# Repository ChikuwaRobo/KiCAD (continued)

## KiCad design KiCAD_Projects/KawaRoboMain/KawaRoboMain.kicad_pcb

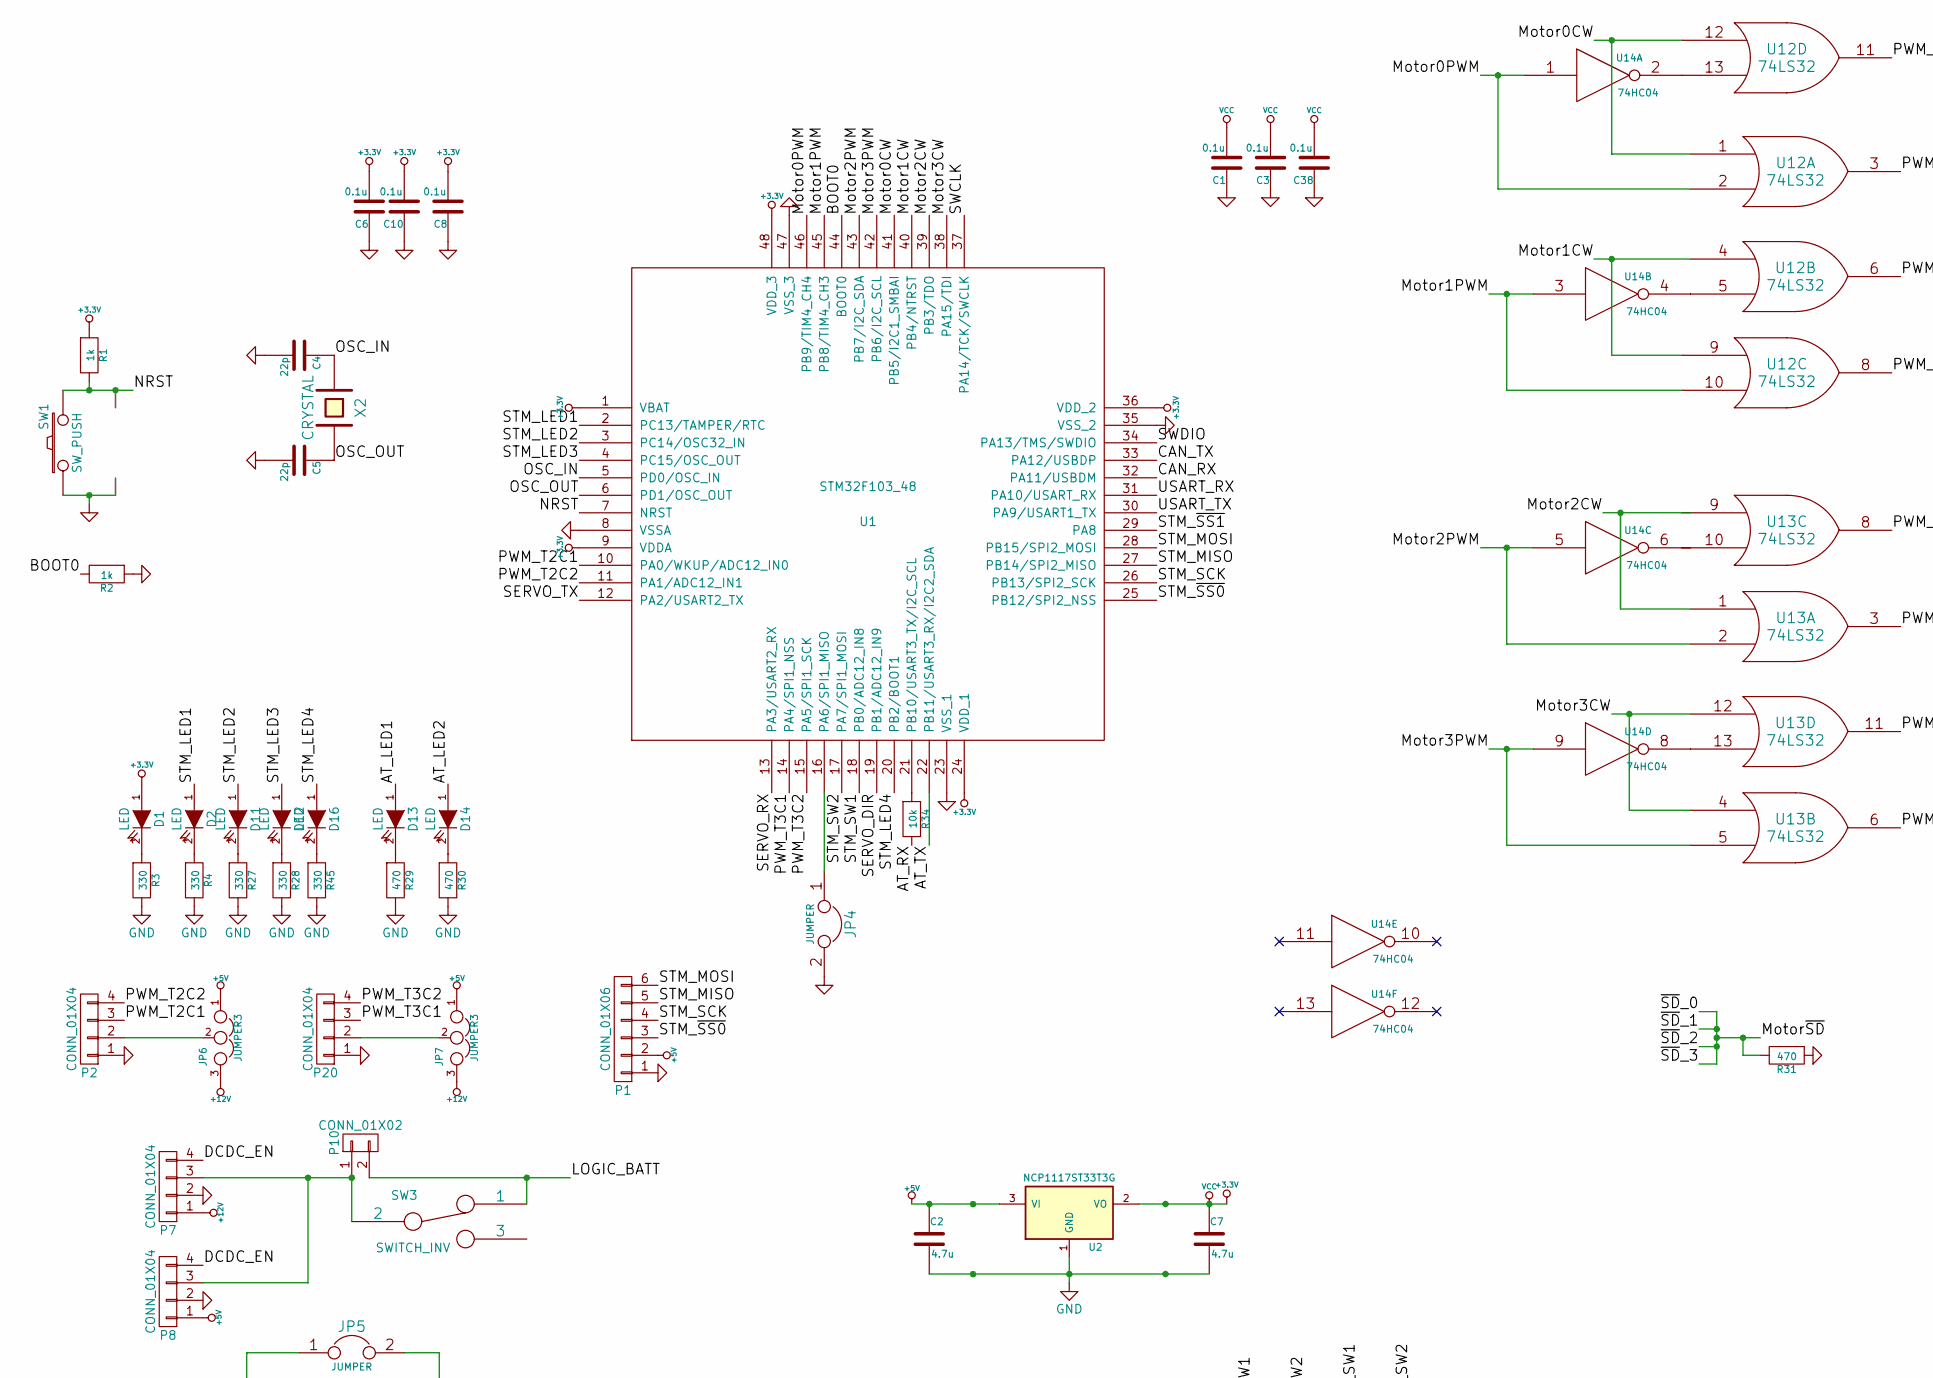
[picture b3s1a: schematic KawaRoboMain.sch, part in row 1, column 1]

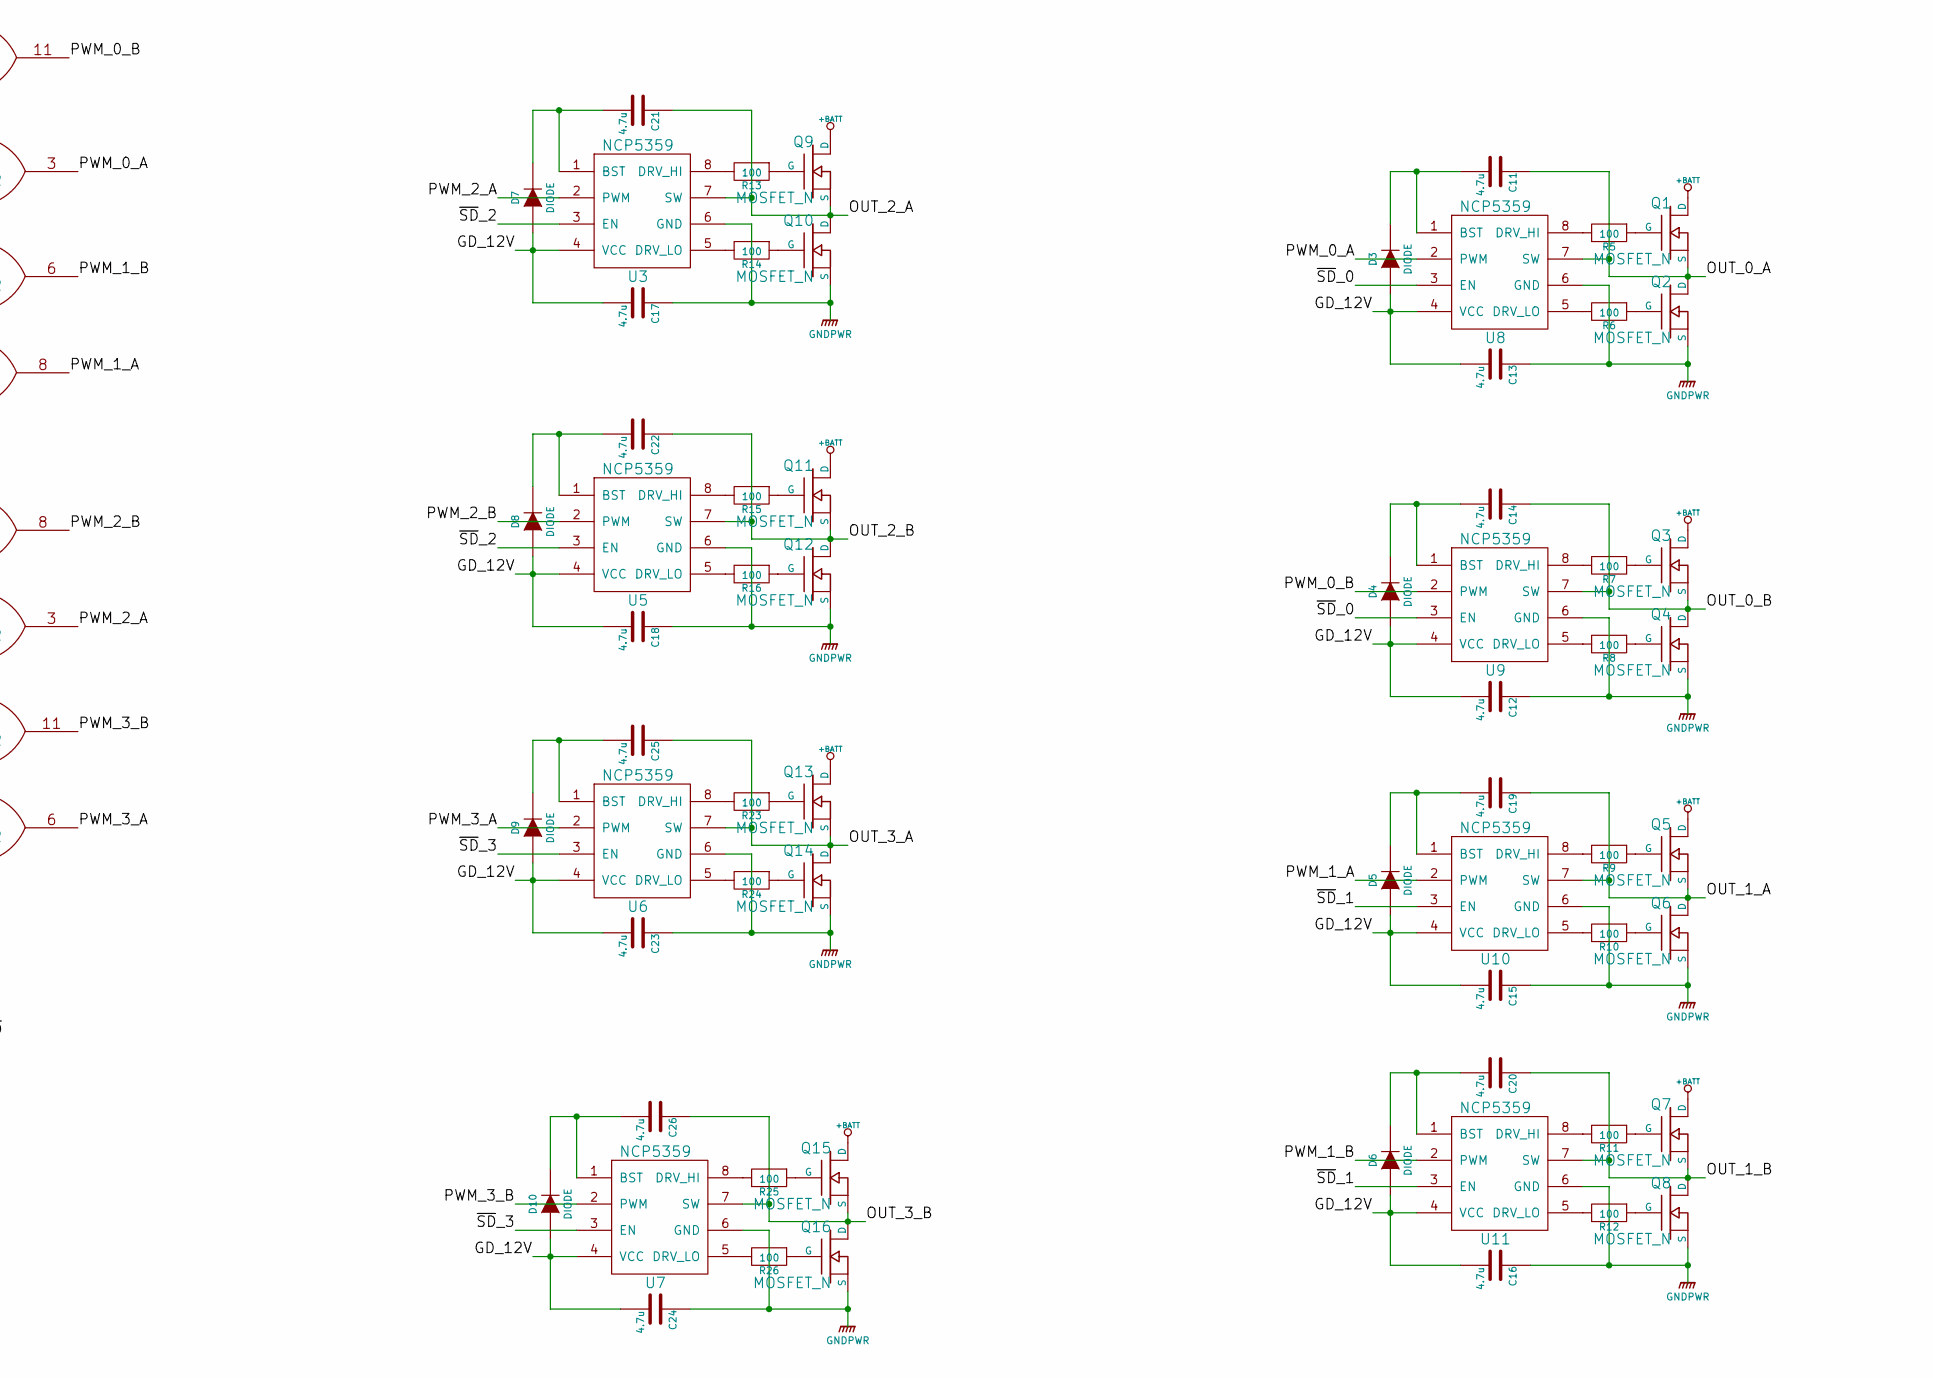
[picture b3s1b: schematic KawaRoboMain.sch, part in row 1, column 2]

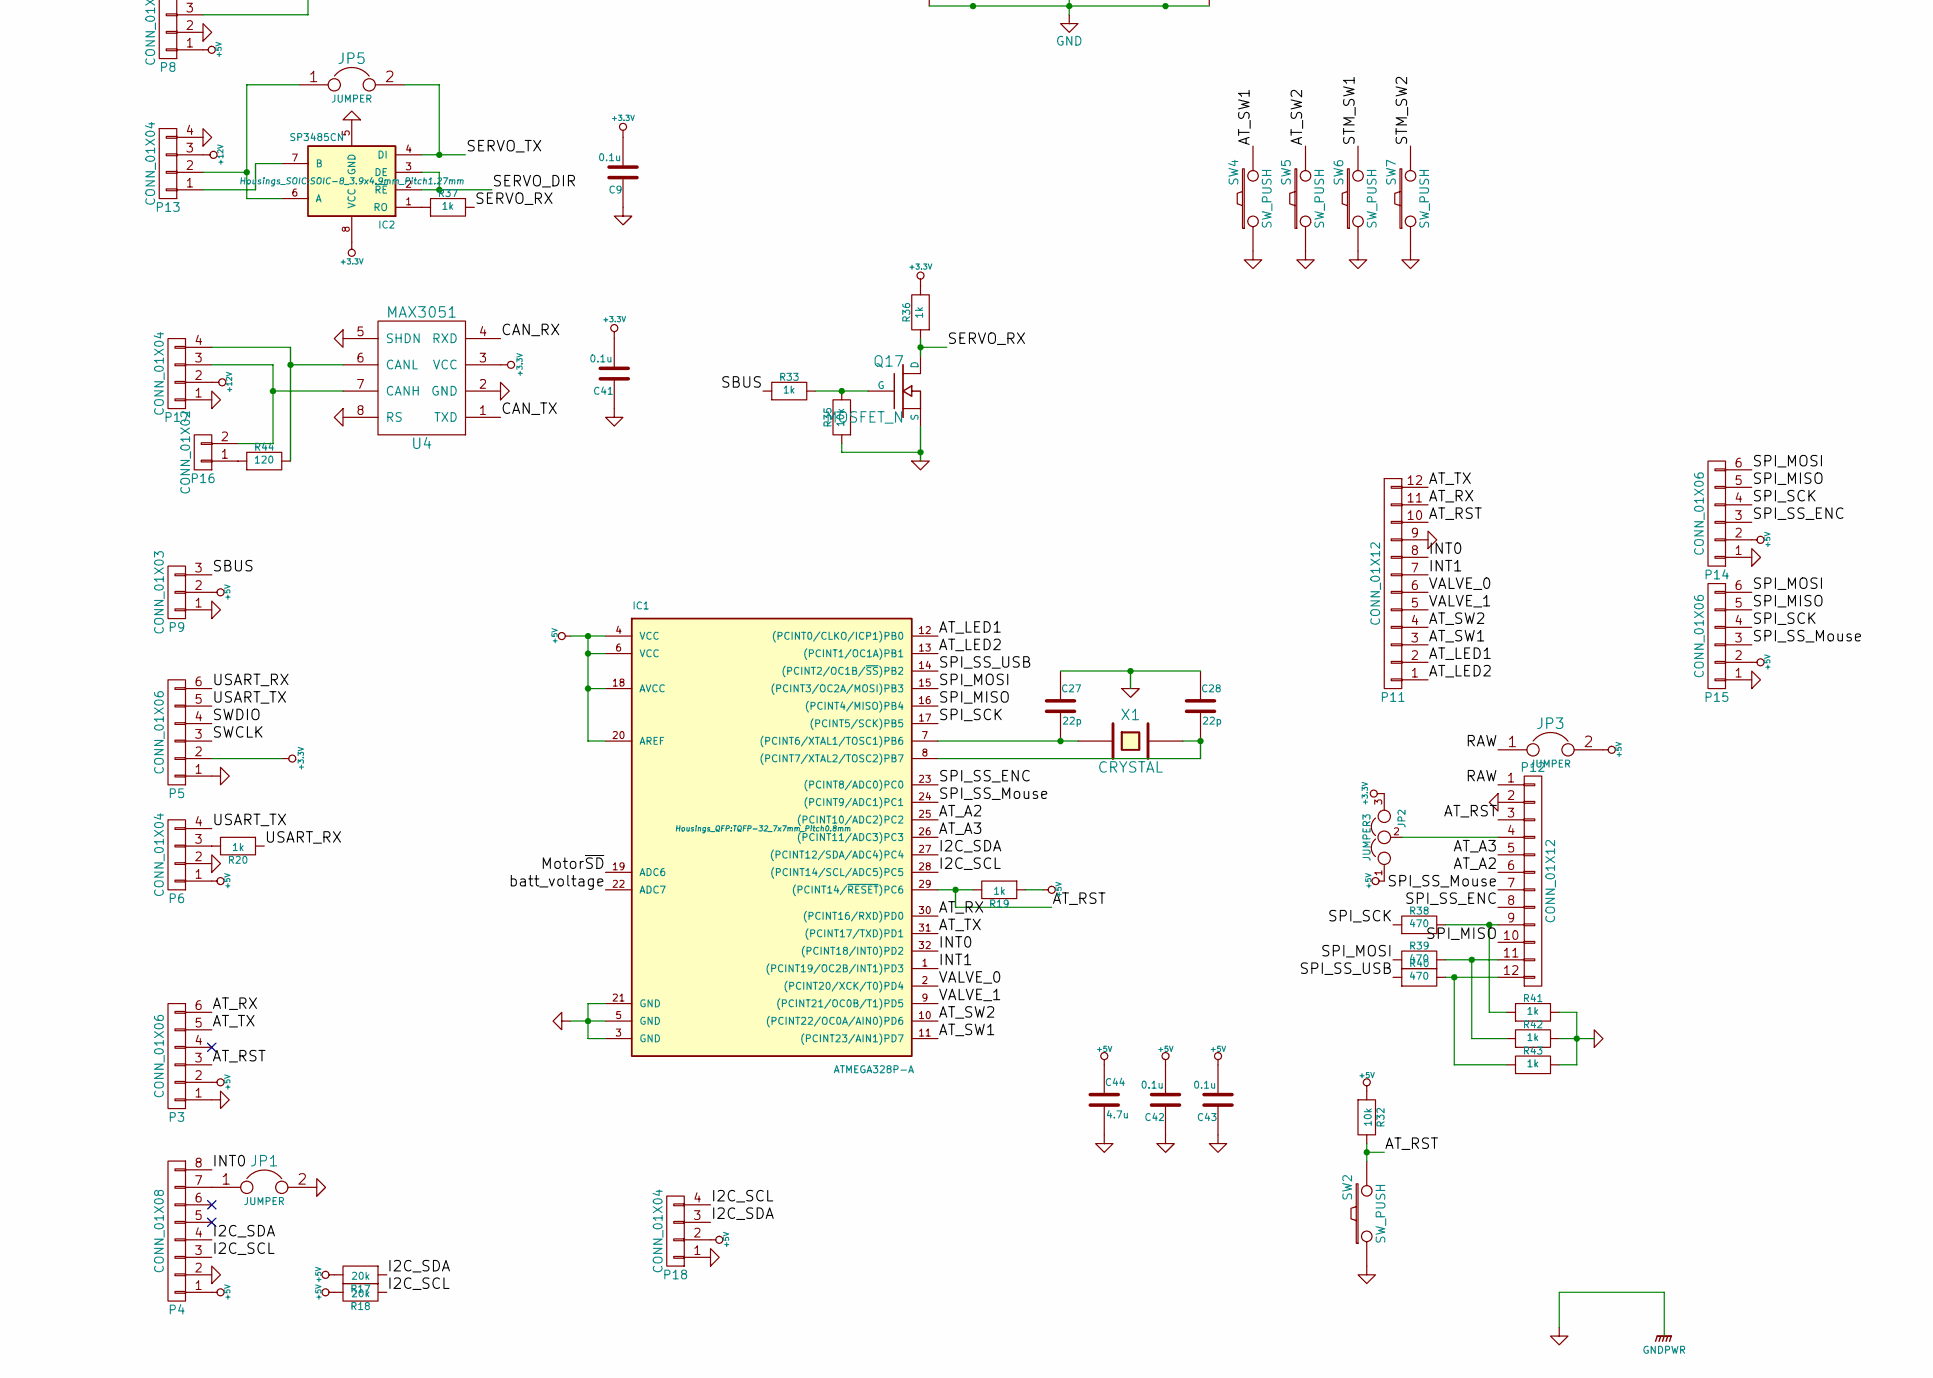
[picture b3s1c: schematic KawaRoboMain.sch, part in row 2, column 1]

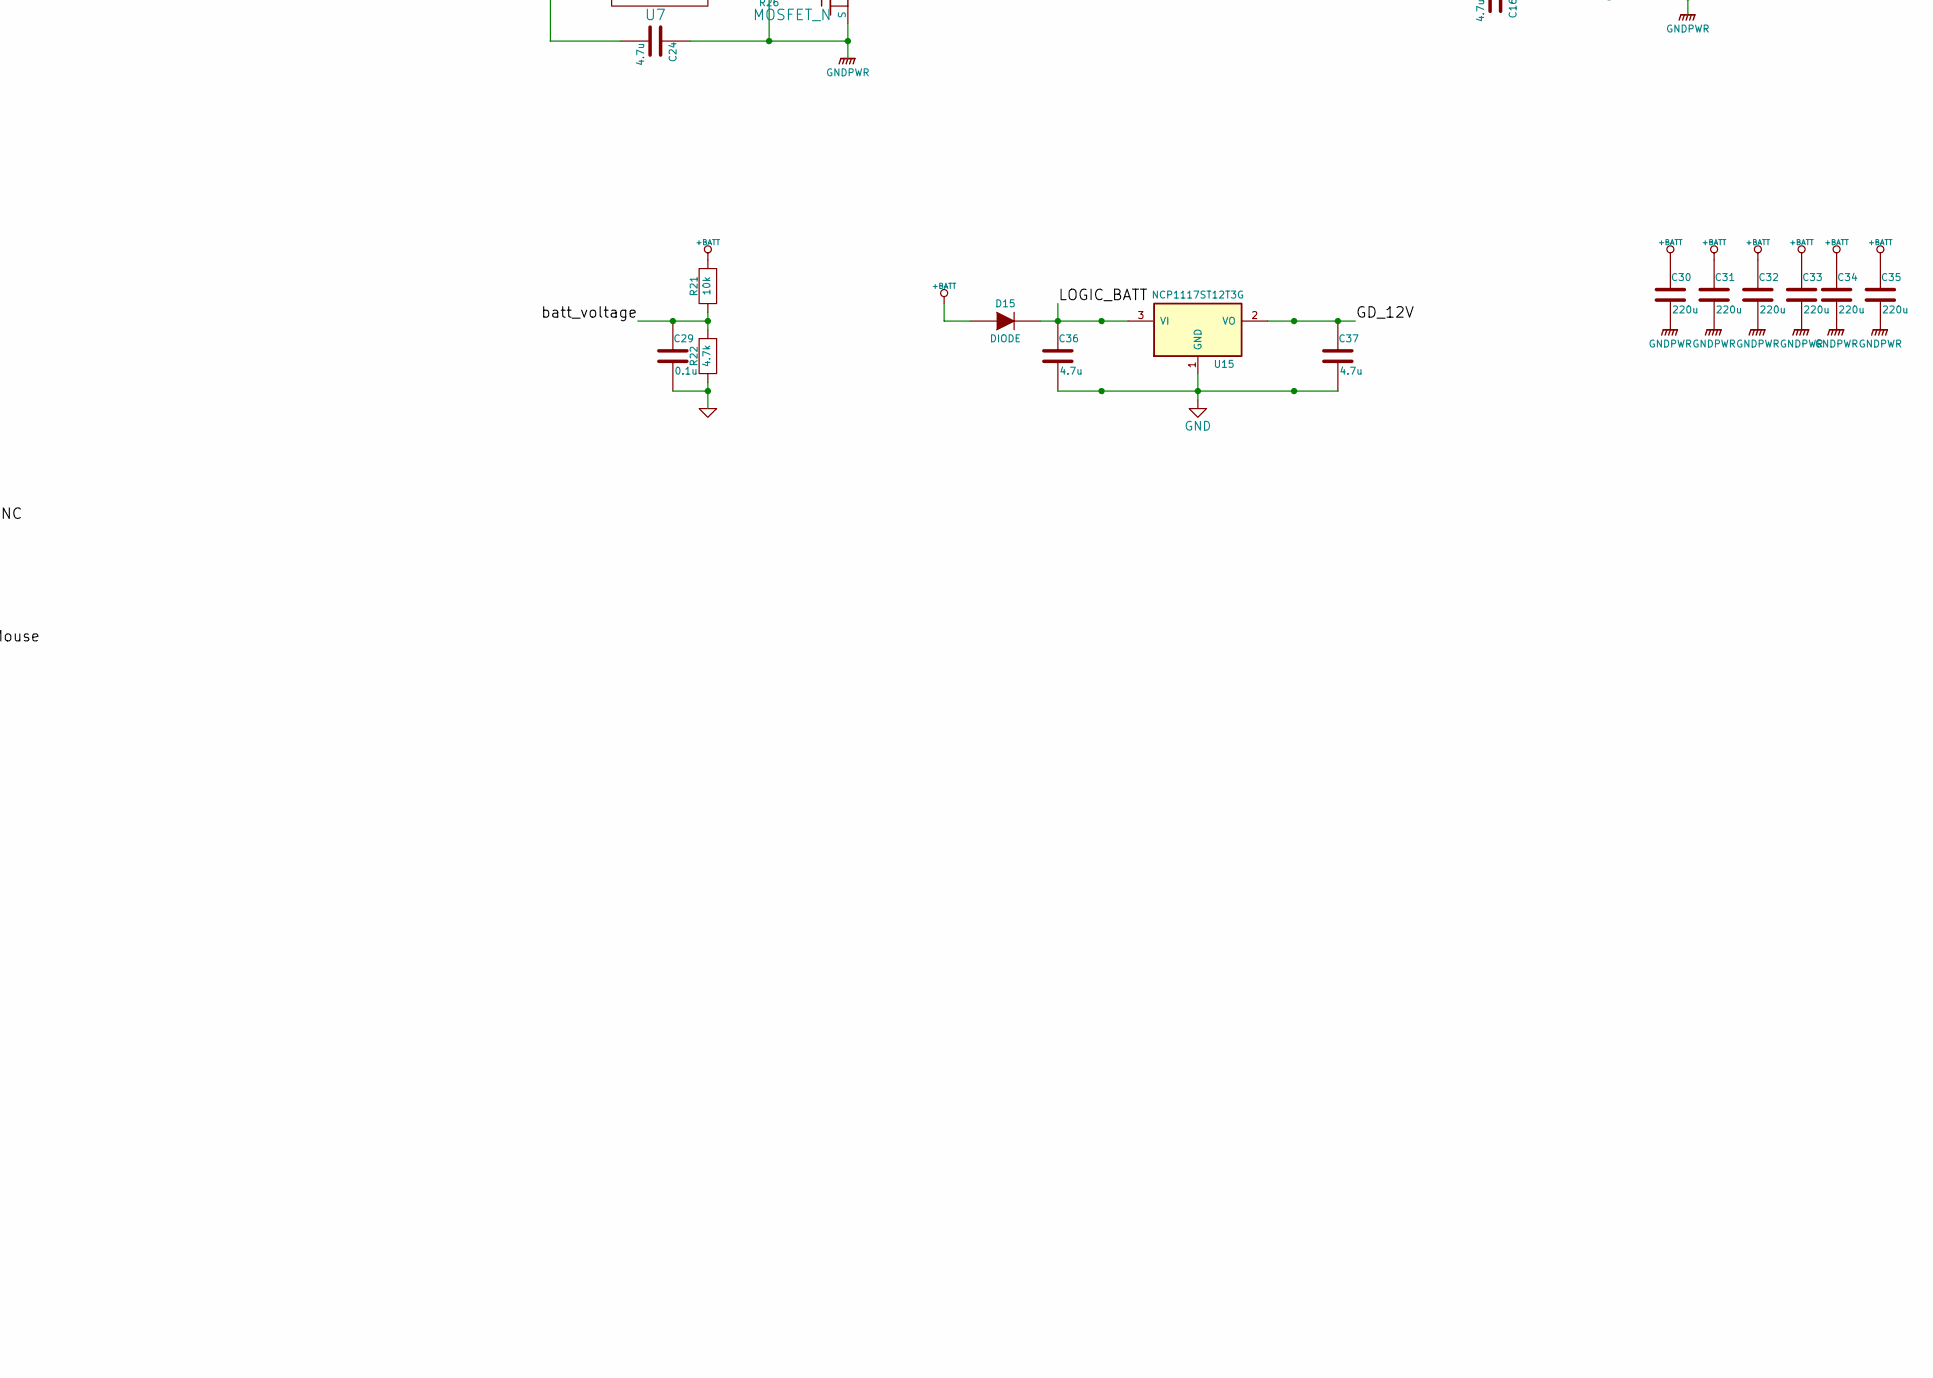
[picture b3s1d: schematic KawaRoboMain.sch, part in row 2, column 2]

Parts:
C1, C3, C6, C8, C9, C10, C29, C38, C41, C42, C43: 0.1u; C1608_WP
C2, C7, C11, C12, C13, C14, C15, C16, C17, C18, C19, C20, C21, C22, C23, C24, C25, C26, C36, C37, C44: 4.7u; C3216
C4, C5, C27, C28: 22p; C1608_WP
C30, C31, C32, C33, C34, C35: 220u; C_Radial_D10_L13_P5
D1, D2, D11, D12, D13, D14, D16: LED; LED_0805
D3, D4, D5, D6, D7, D8, D9, D10: DIODE; C2012
D15: DIODE; SOD-123
IC1: ATMEGA328P-A; TQFP-32_7x7mm_Pitch0.8mm
IC2: SP3485CN; SOIC-8_3.9x4.9mm_Pitch1.27mm
JP1, JP3, JP4, JP5: JUMPER; GS2
JP2, JP6, JP7: JUMPER3; GS3
P1, P14, P15: CONN_01X06; XA_6T
P2, P17, P20: CONN_01X04; XA_4T
P3, P5: CONN_01X06; ZH_6T
P4: CONN_01X08; Socket_Strip_Straight_1x08
P6, P7, P8, P18: CONN_01X04; Socket_Strip_Straight_1x04
P9: CONN_01X03; XA_3T
P10: CONN_01X02; XA_2T
P11, P12: CONN_01X12; Pin_Header_Straight_1x12
P13: CONN_01X04; Molex_SPOX-5267_22-03-5045_04x2.54mm_Straight
P16: CONN_01X02; Socket_Strip_Straight_1x02
Q1, Q2, Q3, Q4, Q5, Q6, Q7, Q8, Q9, Q10, Q11, Q12, Q13, Q14, Q15, Q16: MOSFET_N; SOT-428_GDS_compact
Q17: MOSFET_N; SOT-23_Handsoldering
R1, R2, R19, R20, R33, R36, R37, R41, R42, R43: 1k; C1608_WP
R3, R4, R27, R28, R45: 330; C1608_WP
R5, R6, R7, R8, R9, R10, R11, R12, R13, R14, R15, R16, R23, R24, R25, R26: 100; C1608_WP
R17, R18: 20k; C1608_WP
R21, R32, R34, R35: 10k; C1608_WP
R22: 4.7k; C1608_WP
R29, R30, R31, R38, R39, R40: 470; C1608_WP
R44: 120; C1608_WP
SW1, SW2, SW4, SW5, SW6, SW7: SW_PUSH; RP_SMD_Button
SW3: SWITCH_INV; SW_toggle_3P
U1: STM32F103_48; LQFP-48_7x7mm_Pitch0.5mm
U2: NCP1117ST33T3G; SOT-223_reg
U3, U5, U6, U7, U8, U9, U10, U11: NCP5359; SOIC-8_3.9x4.9mm_Pitch1.27mm
U4: MAX3051; SOIC-8_3.9x4.9mm_Pitch1.27mm
U12, U13: 74LS32; SOIC-14_3.9x8.7mm_Pitch1.27mm
U14: 74HC04; SOIC-14_3.9x8.7mm_Pitch1.27mm
U15: NCP1117ST12T3G; SOT-223_reg
X1: CRYSTAL; Crystal_HC50-U_Vertical
X2: CRYSTAL; ABM3_2pads

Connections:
+3.3V: C1.2, C3.2, C6.2, C7.1, C8.2, C9.2, C10.2, C38.2, C41.2, D1.1 (A), IC2.8 (VCC), JP2.3, P5.2, R1.1, R36.2, U1.1 (VBAT), U1.9 (VDDA), U1.24 (VDD_1), U1.36 (VDD_2), U1.48 (VDD_3), U2.2 (VO), U4.3 (VCC), U12.14 (VCC), U13.14 (VCC), U14.14 (VCC)
+5V: C2.1, C42.2, C43.2, C44.1, IC1.4 (VCC), IC1.6 (VCC), IC1.18 (AVCC), IC1.20 (AREF), JP2.1, JP3.2, JP6.1, JP7.1, P1.2, P3.2, P4.1, P6.1, P8.1, P9.2, P14.2, P15.2, P18.2, R17.2, R18.2, R19.1, R32.1, U2.3 (VI)
+12V: JP6.3, JP7.3, P7.1, P13.3, P17.2
+BATT: C30.1, C31.1, C32.1, C33.1, C34.1, C35.1, D15.2 (A), Q1.D, Q3.D, Q5.D, Q7.D, Q9.D, Q11.D, Q13.D, Q15.D, R21.1
/AT_A2: IC1.25 ((PCINT10/ADC2)PC2), P12.6
/AT_A3: IC1.26 ((PCINT11/ADC3)PC3), P12.5
/AT_LED1: D13.1 (A), IC1.12 ((PCINT0/CLKO/ICP1)PB0), P11.2
/AT_LED2: D14.1 (A), IC1.13 ((PCINT1/OC1A)PB1), P11.1
/AT_RST: IC1.29 ((PCINT14/~RESET~)PC6), P3.3, P11.10, P12.3, R19.2, R32.2, SW2.2
/AT_RX: IC1.30 ((PCINT16/RXD)PD0), P3.6, P11.11, R34.2
/AT_SW1: IC1.11 ((PCINT23/AIN1)PD7), P11.3, SW4.2
/AT_SW2: IC1.10 ((PCINT22/OC0A/AIN0)PD6), P11.4, SW5.2
/AT_TX: IC1.31 ((PCINT17/TXD)PD1), P3.5, P11.12, U1.22 (PB11/USART3_RX/I2C2_SDA)
/BOOT0: R2.2, U1.44 (BOOT0)
/CAN_RX: U1.32 (PA11/USBDM), U4.4 (RXD)
/CAN_TX: U1.33 (PA12/USBDP), U4.1 (TXD)
/DCDC_EN: P7.4, P8.4
/GD_12V: C12.2, C13.2, C15.2, C16.2, C17.2, C18.2, C23.2, C24.2, C37.1, D3.2 (A), D4.2 (A), D5.2 (A), D6.2 (A), D7.2 (A), D8.2 (A), D9.2 (A), D10.2 (A), U3.4 (VCC), U5.4 (VCC), U6.4 (VCC), U7.4 (VCC), U8.4 (VCC), U9.4 (VCC), U10.4 (VCC), U11.4 (VCC), U15.2 (VO)
/I2C_SCL: IC1.28 ((PCINT14/SCL/ADC5)PC5), P4.3, P18.4, R18.1
/I2C_SDA: IC1.27 ((PCINT12/SDA/ADC4)PC4), P4.4, P18.3, R17.1
/INT0: IC1.32 ((PCINT18/INT0)PD2), P4.8, P11.8
/INT1: IC1.1 ((PCINT19/OC2B/INT1)PD3), P11.7
/LOGIC_BATT: C36.1, D15.1 (K), P10.2, SW3.1, U15.3 (VI)
/Motor0CW: U1.41 (PB5/I2C1_SMBAI), U12.1, U12.12
/Motor0PWM: U1.46 (PB9/TIM4_CH4), U12.2, U14.1
/Motor1CW: U1.40 (PB4/NTRST), U12.4, U12.9
/Motor1PWM: U1.45 (PB8/TIM4_CH3), U12.10, U14.3
/Motor2CW: U1.39 (PB3/TDO), U13.1
/Motor2PWM: U1.43 (PB7/I2C_SDA), U13.2, U14.5
/Motor3CW: U1.38 (PA15/TDI), U13.4, U13.12
/Motor3PWM: U1.42 (PB6/I2C_SCL), U13.5, U14.9
/Motor~SD: IC1.19 (ADC6), R31.2, U3.3 (EN), U5.3 (EN), U6.3 (EN), U7.3 (EN), U8.3 (EN), U9.3 (EN), U10.3 (EN), U11.3 (EN)
/NRST: R1.2, SW1.2, U1.7 (NRST)
/OSC_IN: C4.1, U1.5 (PD0/OSC_IN), X2.1
/OSC_OUT: C5.1, U1.6 (PD1/OSC_OUT), X2.2
/OUT_0_A: C11.1, Q1.S, Q2.D, U8.7 (SW)
/OUT_0_B: C14.1, Q3.S, Q4.D, U9.7 (SW)
/OUT_1_A: C19.1, Q5.S, Q6.D, U10.7 (SW)
/OUT_1_B: C20.1, Q7.S, Q8.D, U11.7 (SW)
/OUT_2_A: C21.1, Q9.S, Q10.D, U3.7 (SW)
/OUT_2_B: C22.1, Q11.S, Q12.D, U5.7 (SW)
/OUT_3_A: C25.1, Q13.S, Q14.D, U6.7 (SW)
/OUT_3_B: C26.1, Q15.S, Q16.D, U7.7 (SW)
/PWM_0_A: U8.2 (PWM), U12.3
/PWM_0_B: U9.2 (PWM), U12.11
/PWM_1_A: U10.2 (PWM), U12.8
/PWM_1_B: U11.2 (PWM), U12.6
/PWM_2_A: U3.2 (PWM), U13.3
/PWM_2_B: U5.2 (PWM), U13.8
/PWM_3_A: U6.2 (PWM), U13.6
/PWM_3_B: U7.2 (PWM), U13.11
/PWM_T2C1: P2.3, U1.10 (PA0/WKUP/ADC12_IN0)
/PWM_T2C2: P2.4, U1.11 (PA1/ADC12_IN1)
/PWM_T3C1: P20.3, U1.14 (PA4/SPI1_NSS)
/PWM_T3C2: P20.4, U1.15 (PA5/SPI1_SCK)
/RAW: JP3.1, P12.1
/SBUS: P9.3, R33.1
/SERVO_DIR: IC2.2 (~RE~), IC2.3 (DE), U1.19 (PB1/ADC12_IN9)
/SERVO_RX: Q17.D, R36.1, R37.2, U1.13 (PA3/USART2_RX)
/SERVO_TX: IC2.4 (DI), JP5.2, U1.12 (PA2/USART2_TX)
/SPI_MISO: IC1.16 ((PCINT4/MISO)PB4), P12.10, P14.5, P15.5
/SPI_MOSI: IC1.15 ((PCINT3/OC2A/MOSI)PB3), P14.6, P15.6, R39.1
/SPI_SCK: IC1.17 ((PCINT5/SCK)PB5), P14.4, P15.4, R38.1
/SPI_SS_ENC: IC1.23 ((PCINT8/ADC0)PC0), P12.8, P14.3
/SPI_SS_Mouse: IC1.24 ((PCINT9/ADC1)PC1), P12.7, P15.3
/SPI_SS_USB: IC1.14 ((PCINT2/OC1B/~SS~)PB2), R40.1
/STM_LED1: D2.1 (A), U1.2 (PC13/TAMPER/RTC)
/STM_LED2: D11.1 (A), U1.3 (PC14/OSC32_IN)
/STM_LED3: D12.1 (A), U1.4 (PC15/OSC_OUT)
/STM_LED4: D16.1 (A), U1.20 (PB2/BOOT1)
/STM_MISO: P1.5, U1.27 (PB14/SPI2_MISO)
/STM_MOSI: P1.6, U1.28 (PB15/SPI2_MOSI)
/STM_SCK: P1.4, U1.26 (PB13/SPI2_SCK)
/STM_SW1: SW6.2, U1.18 (PB0/ADC12_IN8)
/STM_SW2: SW7.2, U1.17 (PA7/SPI1_MOSI)
/STM_~SS0: P1.3, U1.25 (PB12/SPI2_NSS)
/SWCLK: P5.3, U1.37 (PA14/TCK/SWCLK)
/SWDIO: P5.4, U1.34 (PA13/TMS/SWDIO)
/USART_RX: P5.6, R20.1, U1.31 (PA10/USART_RX)
/USART_TX: P5.5, P6.4, U1.30 (PA9/USART1_TX)
/VALVE_0: IC1.2 ((PCINT20/XCK/T0)PD4), P11.6
/VALVE_1: IC1.9 ((PCINT21/OC0B/T1)PD5), P11.5
/batt_voltage: C29.1, IC1.22 (ADC7), R21.2, R22.1
GND: C1.1, C2.2, C3.1, C4.2, C5.2, C6.1, C7.2, C8.1, C9.1, C10.1, C12.1, C13.1, C15.1, C16.1, C17.1, C18.1, C23.1, C24.1, C27.1, C28.1, C29.2, C30.2, C31.2, C32.2, C33.2, C34.2, C35.2, C36.2, C37.2, C38.1, C41.1, C42.1, C43.1, C44.2, IC1.3 (GND), IC1.5 (GND), IC1.21 (GND), IC2.5 (GND), JP1.2, JP4.2, P1.1, P2.1, P3.1, P4.2, P5.1, P6.2, P7.2, P8.2, P9.1, P11.9, P12.2, P13.4, P14.1, P15.1, P17.1, P18.1, P20.1, Q2.S, Q4.S, Q6.S, Q8.S, Q10.S, Q12.S, Q14.S, Q16.S, Q17.S, R2.1, R3.2, R4.2, R22.2, R27.2, R28.2, R29.2, R30.2, R31.1, R35.1, R41.2, R42.2, R43.2, R45.2, SW1.1, SW2.1, SW4.1, SW5.1, SW6.1, SW7.1, U1.8 (VSSA), U1.23 (VSS_1), U1.35 (VSS_2), U1.47 (VSS_3), U2.1 (GND), U3.6 (GND), U4.2 (GND), U4.5 (SHDN), U4.8 (RS), U5.6 (GND), U6.6 (GND), U7.6 (GND), U8.6 (GND), U9.6 (GND), U10.6 (GND), U11.6 (GND), U12.7 (GND), U13.7 (GND), U14.7 (GND), U15.1 (GND)
unnamed: C11.2, D3.1 (K), U8.1 (BST)
unnamed: C14.2, D4.1 (K), U9.1 (BST)
unnamed: C19.2, D5.1 (K), U10.1 (BST)
unnamed: C20.2, D6.1 (K), U11.1 (BST)
unnamed: C21.2, D7.1 (K), U3.1 (BST)
unnamed: C22.2, D8.1 (K), U5.1 (BST)
unnamed: C25.2, D9.1 (K), U6.1 (BST)
unnamed: C26.2, D10.1 (K), U7.1 (BST)
unnamed: C27.2, IC1.7 ((PCINT6/XTAL1/TOSC1)PB6), X1.1
unnamed: C28.2, IC1.8 ((PCINT7/XTAL2/TOSC2)PB7), X1.2
unnamed: D1.2 (K), R3.1
unnamed: D2.2 (K), R4.1
unnamed: D11.2 (K), R27.1
unnamed: D12.2 (K), R28.1
unnamed: D13.2 (K), R29.1
unnamed: D14.2 (K), R30.1
unnamed: D16.2 (K), R45.1
unnamed: IC2.1 (RO), R37.1
unnamed: IC2.6 (A), JP5.1, P13.2
unnamed: IC2.7 (B), P13.1
unnamed: JP1.1, P4.7
unnamed: JP2.2, P12.4
unnamed: JP4.1, U1.16 (PA6/SPI1_MISO)
unnamed: JP6.2, P2.2
unnamed: JP7.2, P20.2
unnamed: P6.3, R20.2
unnamed: P7.3, P8.3, P10.1, SW3.2
unnamed: P12.9, R38.2, R41.1
unnamed: P12.11, R39.2, R42.1
unnamed: P12.12, R40.2, R43.1
unnamed: P16.1, R44.1
unnamed: P16.2, P17.3, U4.7 (CANH)
unnamed: P17.4, R44.2, U4.6 (CANL)
unnamed: Q1.G, R5.1
unnamed: Q2.G, R6.1
unnamed: Q3.G, R7.1
unnamed: Q4.G, R8.1
unnamed: Q5.G, R9.1
unnamed: Q6.G, R10.1
unnamed: Q7.G, R11.1
unnamed: Q8.G, R12.1
unnamed: Q9.G, R13.1
unnamed: Q10.G, R14.1
unnamed: Q11.G, R15.1
unnamed: Q12.G, R16.1
unnamed: Q13.G, R23.1
unnamed: Q14.G, R24.1
unnamed: Q15.G, R25.1
unnamed: Q16.G, R26.1
unnamed: Q17.G, R33.2, R35.2
unnamed: R5.2, U8.8 (DRV_HI)
unnamed: R6.2, U8.5 (DRV_LO)
unnamed: R7.2, U9.8 (DRV_HI)
unnamed: R8.2, U9.5 (DRV_LO)
unnamed: R9.2, U10.8 (DRV_HI)
unnamed: R10.2, U10.5 (DRV_LO)
unnamed: R11.2, U11.8 (DRV_HI)
unnamed: R12.2, U11.5 (DRV_LO)
unnamed: R13.2, U3.8 (DRV_HI)
unnamed: R14.2, U3.5 (DRV_LO)
unnamed: R15.2, U5.8 (DRV_HI)
unnamed: R16.2, U5.5 (DRV_LO)
unnamed: R23.2, U6.8 (DRV_HI)
unnamed: R24.2, U6.5 (DRV_LO)
unnamed: R25.2, U7.8 (DRV_HI)
unnamed: R26.2, U7.5 (DRV_LO)
unnamed: R34.1, U1.21 (PB10/USART3_TX/I2C_SCL)
unnamed: U12.5, U14.4
unnamed: U12.13, U14.2
unnamed: U13.13, U14.8

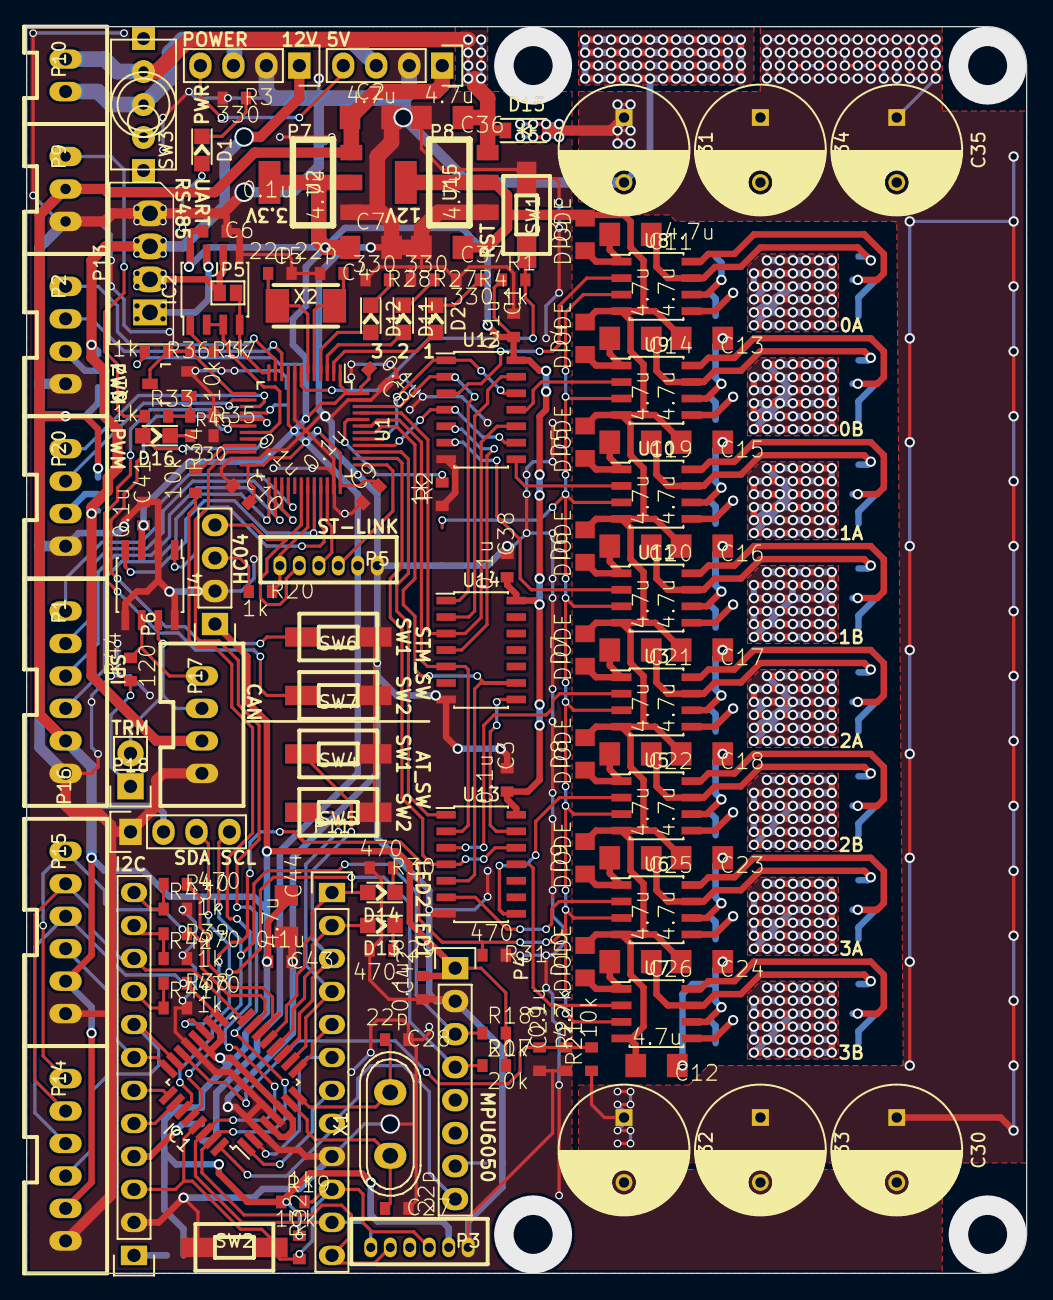
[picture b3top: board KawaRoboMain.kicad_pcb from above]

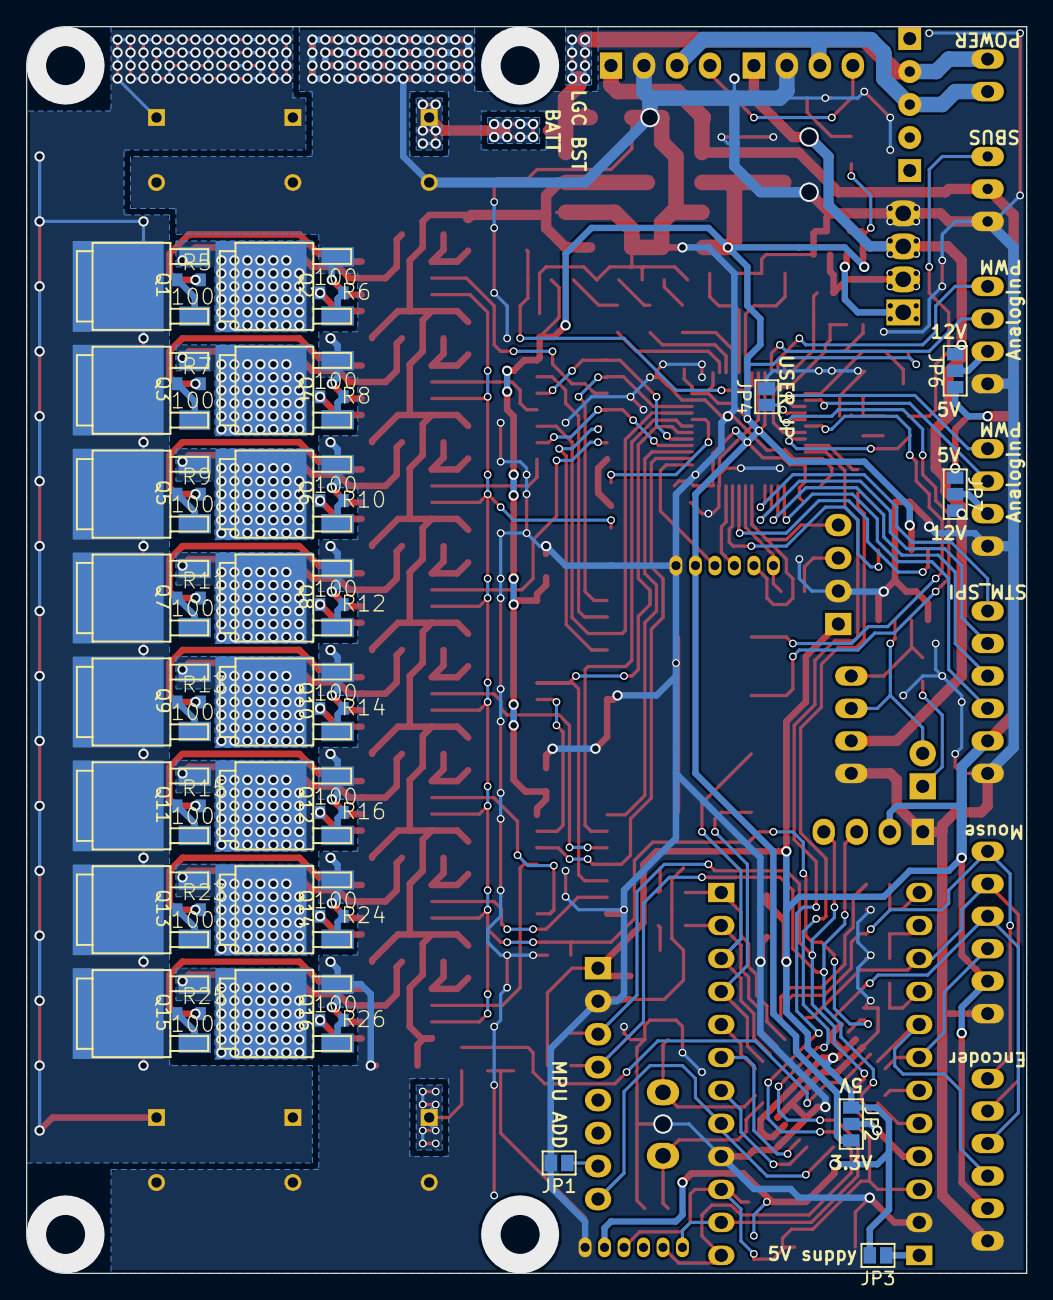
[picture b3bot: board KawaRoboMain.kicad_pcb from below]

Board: 2 copper layers, 77.0 x 96.0 mm, 172 parts (38 on the bottom side), 154 nets.
